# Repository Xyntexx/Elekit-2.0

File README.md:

# Elekit-2.0

[Auto generated schematic](output/schematic.pdf)

https://dl.espressif.com/dl/schematics/SCH_ESP32-C3-DEVKITC-02_V1_1_20210126A.pdf

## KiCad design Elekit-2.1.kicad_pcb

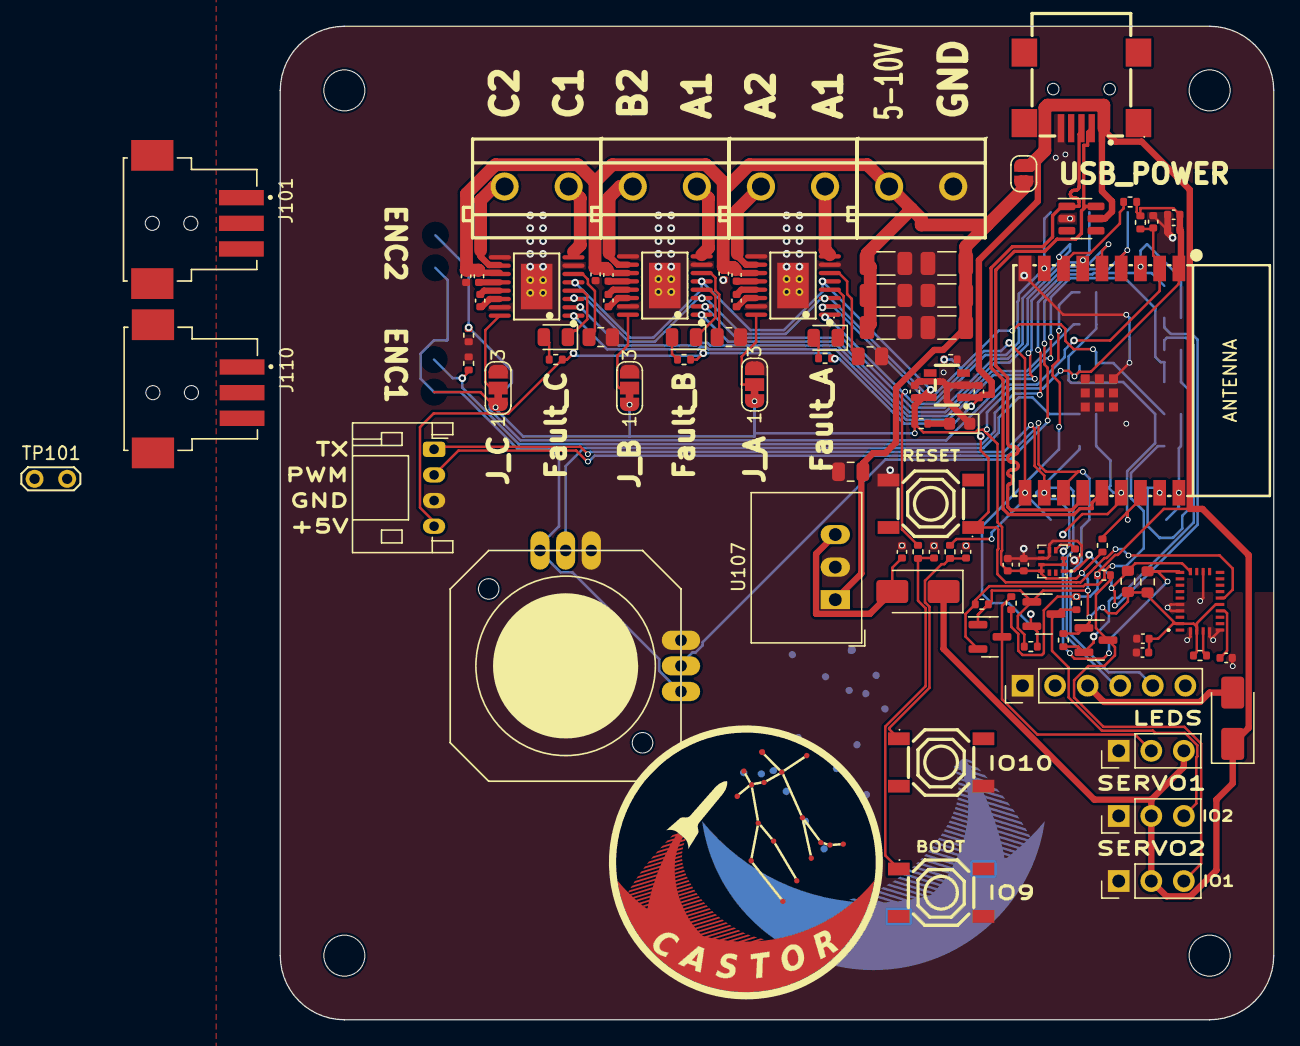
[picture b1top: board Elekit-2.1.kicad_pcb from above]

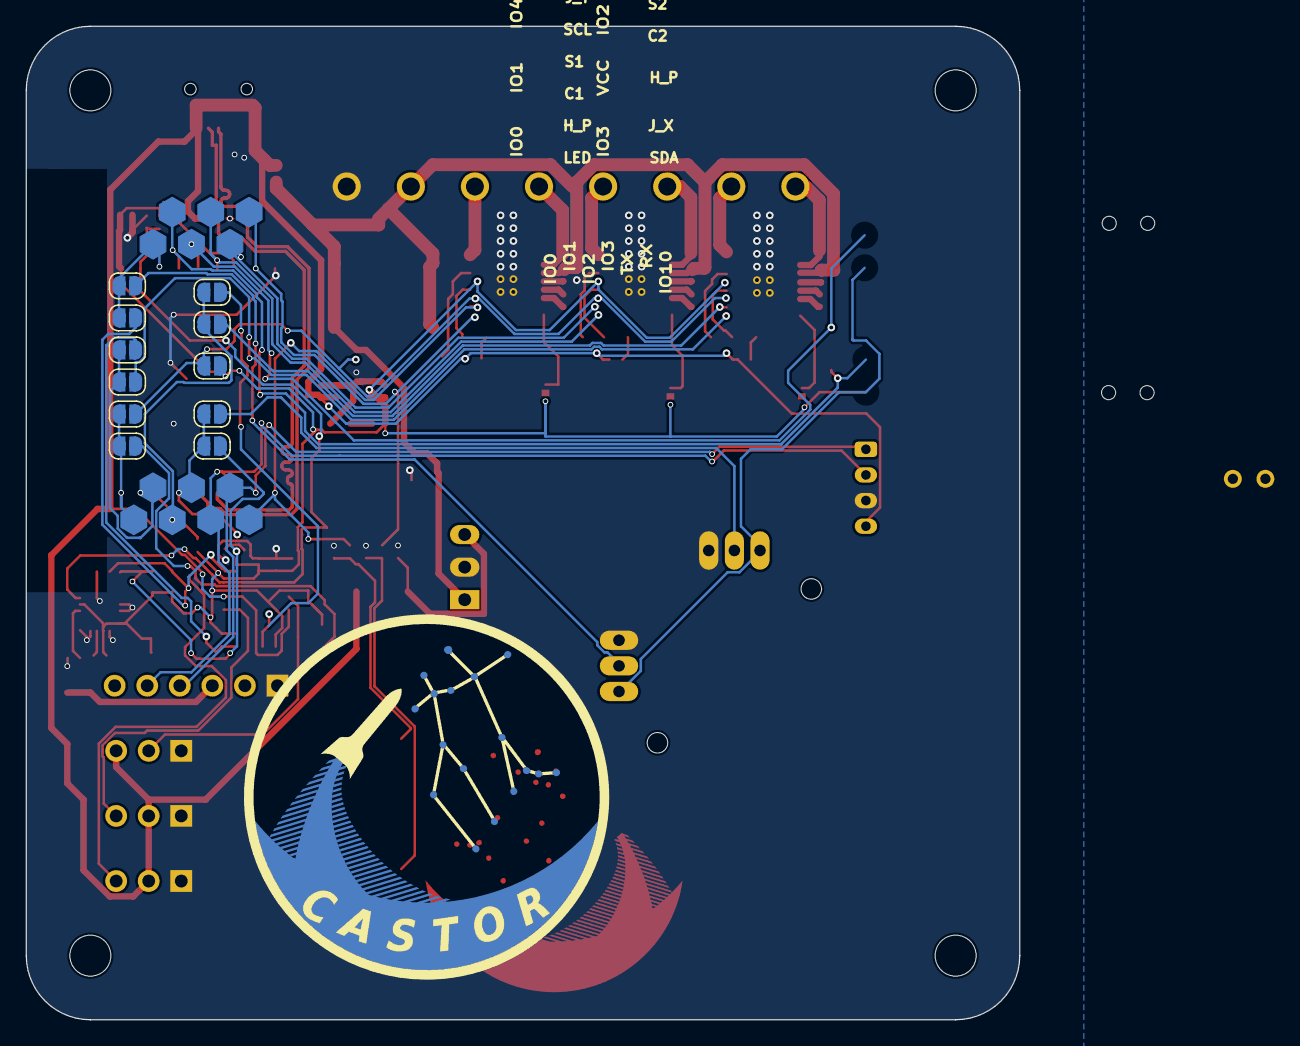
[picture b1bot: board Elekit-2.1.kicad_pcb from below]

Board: 2 copper layers, 77.5 x 77.5 mm, 123 parts (25 on the bottom side), 68 nets.

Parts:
C8, C9: 1u 25V; C_0402_1005Metric
C101, C102, C118: 22n 50V; C_0402_1005Metric
C103, C104, C105, C106, C112, C114, C116, C117, C119, C120, C125, C126, C127, C128: 100n 16V; C_0402_1005Metric
C107, C108, C109, C110, C121, C122: 47u 10V; C_1206_3216Metric
C111, C115: 10u 6.3V; C_0402_1005Metric
C113: 220n 16V; C_0402_1005Metric
C123: 0.47u 50v; C_0805_2012Metric
C124: 0.1u 50V; C_0402_1005Metric
D4: LED Emerald; LED_0603_1608Metric
D8, D104: SS34; D_SMA
D101, D102, D103: LED; LED_0805_2012Metric
H1, H2, H3, H4: MountingHole_Pad; MountingHole_3.2mm_M3
IC101: BNO085
J2, J3, J4, J103: Screw_Terminal_01x02; CONN-TH_P5.00_KF301-5.0-2P
J5, J9, J104: Conn_01x03_Male; PinHeader_1x03_P2.54mm_Vertical
J6: Conn_01x06_Male; PinHeader_1x06_P2.54mm_Vertical
J101, J110: Conn_01x03_Socket; TE_292173-3
J105, J106, J107, J108, J111, J112, J113, J117, J118, J119, J120, J121, J122: Conn_01x01_Pin; Hex Pad
J109: Conn_01x04_Socket; JST_PH_S4B-PH-K_1x04_P2.00mm_Horizontal
JP101, JP102, JP103, JP104, JP108, JP109, JP110, JP111, JP112, JP113, JP114, JP115: VIN DIODE BYPASS; SolderJumper-2_P1.3mm_Open_RoundedPad1.0x1.5mm
JP105, JP106, JP107: SolderJumper_3_Bridged12; SolderJumper-3_P1.3mm_Bridged12_RoundedPad1.0x1.5mm_NumberL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
LOGO1: CASTOR; Castor logo (2)
LOGO101: CASTOR; Castor logo (3)
Q1, Q3, Q101: 2N7002; SOT-23
R101, R102, R115, R118, R120, R121: 1k; R_0402_1005Metric
R103, R106, R107, R108, R109, R110, R111, R112, R113, R114, R116, R117, R124: 10k; R_0402_1005Metric
R104, R105, R119: 1k5; R_0805_2012Metric
R122, R123: 3k9; R_0603_1608Metric
RV101: R_Potentiometer_Dual; JOYSTICK_ANALOG_MINITHM
TP101: TestPoint_2Pole; TestPoint_2Pads_Pitch2.54mm_Drill0.8mm
U1: MINI_5PTP; MINI-USB-SMD_MINI-5PTP
U5: SRV05-4-P-T7; SOT-23-6
U7: ME6211C33M5G-N; SOT-23-5_L3.0-W1.7-P0.95-LS2.8-BR
U8, U10, U106: TS-1187A-B-A-B; SW-SMD_4P-L5.1-W5.1-P3.70-LS6.5-TL-2
U9: ESP32-C3-WROOM-02-N4(4MB); BULETM-SMD_ESPRESSIF_ESP32-C3-WROOM-02-N4-4MB
U101, U102, U104: DRV8876PWPR; HTSSOP-16_L5.0-W4.4-P0.65-LS6.4-BL-EP
U103: LSM303AGRTR; LGA-12_L2.0-W2.0-P0.50-BL
U107: R-78E5.0-0.5; Converter_DCDC_RECOM_R-78E-0.5_THT

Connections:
+3.3V: C9.1, C111.1, C112.1, C114.1, C115.2, C126.2, C127.2, IC101.3 (VDD), IC101.10 (CLKSEL0), IC101.28 (VDDIO), J101.1, J110.1, JP105.1 (A), JP106.1 (A), JP107.1 (A), JP115.2 (B), Q1.1 (G), Q3.1 (G), Q101.1 (G), R106.1, R107.2, R108.1, R109.1, R112.1, R113.1, R115.1, R122.1, R123.1, R124.1, RV101.1, RV101.6, U7.5 (VOUT), U9.1 (3V3), U101.5 (VREF), U102.5 (VREF), U103.2 (CS_XL), U103.3 (CS_MAG), U103.9 (Vdd), U103.10 (Vdd_IO), U104.5 (VREF)
+5V: C8.2, D8.1 (K), D104.1 (K), J5.2, J9.2, J104.3, J109.4, JP108.2 (B), R101.2, R102.2, R110.1, R111.1, R114.1, R118.2, U1.1 (VCC), U5.5 (VP), U7.1 (VIN)
+BATT: C103.2, C104.1, C105.2, C106.1, C107.2, C108.2, C109.2, C110.2, C119.2, C120.1, C121.2, C122.2, C123.2, J4.2, JP108.1 (A), U101.11 (VM), U102.11 (VM), U104.11 (VM), U107.1 (IN)
/A1: J2.1, U101.8 (OUT1)
/A1_C: J122.1, R120.1, U9.8 (IO9), U101.1 (EN/IN1)
/A2: J2.2, U101.10 (OUT2)
/A2_C: J105.1, R121.1, U9.10 (IO10), U101.2 (PH/IN2)
/A_analog: R105.2, U101.6 (IPROPI)
/B1: J3.1, U102.8 (OUT1)
/B1_C: J120.1, U9.6 (IO7), U102.1 (EN/IN1)
/B2: J3.2, U102.10 (OUT2)
/B2_C: J121.1, R107.1, U9.7 (IO8), U102.2 (PH/IN2)
/B_analog: R104.1, U102.6 (IPROPI)
/C1: J103.1, U104.8 (OUT1)
/C1_C: JP102.1 (A), U104.1 (EN/IN1)
/C2: J103.2, U104.10 (OUT2)
/C2_C: JP104.1 (A), U104.2 (PH/IN2)
/CHIP_PU: C117.2, IC101.11 (NRST), R106.2, U9.2 (EN), U10.1 (A)
/C_analog: R119.1, U104.6 (IPROPI)
/D+: U1.3 (D+), U5.1 (IO1), U9.14 (IO19)
/D-: U1.2 (D-), U5.6 (IO4), U9.13 (IO18)
/GPIO0: J113.1, JP113.2 (B), JP114.2 (B), U9.18 (IO0)
/GPIO1: J111.1, JP101.2 (B), JP102.2 (B), U9.17 (IO1)
/GPIO2: J112.1, JP103.2 (B), JP104.2 (B), R108.2, U9.16 (IO2)
/GPIO3: J108.1, JP109.2 (B), JP110.2 (B), U9.15 (IO3)
/GPIO4: J117.1, JP111.2 (B), JP112.2 (B), U9.3 (IO4)
/GPIO5: J101.2, J118.1, R117.2, U9.4 (IO5)
/GPIO6: J110.2, J119.1, R116.1, U9.5 (IO6)
/H-Bridge_nsleep: JP113.1 (A), JP115.1 (A), R103.1, U101.3 (nSLEEP), U102.3 (nSLEEP), U104.3 (nSLEEP)
/JoyX: JP109.1 (A), RV101.2
/JoyY: JP111.1 (A), RV101.5
/LED_in: JP114.1 (A), Q101.2 (S), R109.2
/LED_out: J104.2, Q101.3 (D), R110.2
/RX: J6.4, J106.1, J109.1, U9.11 (RXD)
/SCL: IC101.19 (H_SCL/SCK/RX), JP112.1 (A), R122.2, U103.1 (SCL/SPC)
/SDA: IC101.20 (H_SDA/H_MISO/TX_), JP110.1 (A), R123.2, U103.4 (SDA/SDI/SDO)
/SERVO1: J5.3, Q1.3 (D), R114.2
/SERVO1_C: JP101.1 (A), Q1.2 (S), R113.2
/SERVO2: J9.3, Q3.3 (D), R111.2
/SERVO2_C: JP103.1 (A), Q3.2 (S), R112.2
/TX: J6.5, J107.1, J109.2, U9.12 (TXD)
GND: C8.1, C9.2, C103.1, C105.1, C107.1, C108.1, C109.1, C110.1, C111.2, C112.2, C113.1, C114.2, C115.1, C116.1, C117.1, C119.1, C121.1, C122.1, C123.1, C124.1, C125.1, C126.1, C127.1, C128.1, D4.1 (K), IC101.2 (GND_1), IC101.5 (PS1), IC101.6 (PS0/WAKE), IC101.17 (SA0/H_MOSI_), IC101.25 (GND_2), IC101.26 (XOUT32/CLKSEL1), J4.1, J5.1, J6.1, J9.1, J101.3, J104.1, J109.3, J110.3, JP105.3 (B), JP106.3 (B), JP107.3 (B), R103.2, R104.2, R105.1, R116.2, R117.1, R119.2, RV101.3, RV101.4, TP101.1, U1.5 (GND), U5.2 (VN), U7.2 (VSS), U8.4 (D), U9.9 (GND), U9.19 (EP), U10.4 (D), U101.7 (IMODE), U101.9 (PGND), U101.15 (GND), U101.17 (EP), U102.7 (IMODE), U102.9 (PGND), U102.15 (GND), U102.17 (EP), U103.6 (GND), U103.8 (GND), U104.7 (IMODE), U104.9 (PGND), U104.15 (GND), U104.17 (EP), U106.4 (D), U107.2 (GND)
unnamed: D4.2 (A), R115.2
unnamed: D8.2 (A), J6.3
unnamed: D101.2 (A), R101.1
unnamed: D101.1 (K), U101.4 (nFAULT)
unnamed: D102.2 (A), R102.1
unnamed: D102.1 (K), U102.4 (nFAULT)
unnamed: D103.2 (A), R118.1
unnamed: D103.1 (K), U104.4 (nFAULT)
unnamed: C124.2, D104.2 (A), U107.3 (OUT)
unnamed: IC101.4 (BOOTN), R124.2, TP101.2
unnamed: C128.2, IC101.9 (CAP)
unnamed: JP105.2 (C), U102.16 (PMODE)
unnamed: JP106.2 (C), U101.16 (PMODE)
unnamed: JP107.2 (C), U104.16 (PMODE)
unnamed: C116.2, R120.2, U8.1 (A)
unnamed: C101.1, U101.13 (CPH)
unnamed: C101.2, U101.14 (CPL)
unnamed: C104.2, U101.12 (VCP)
unnamed: C102.1, U102.13 (CPH)
unnamed: C102.2, U102.14 (CPL)
unnamed: C106.2, U102.12 (VCP)
unnamed: C113.2, U103.5 (C1)
unnamed: C118.1, U104.13 (CPH)
unnamed: C118.2, U104.14 (CPL)
unnamed: C120.2, U104.12 (VCP)
unnamed: C125.2, R121.2, U106.1 (A)

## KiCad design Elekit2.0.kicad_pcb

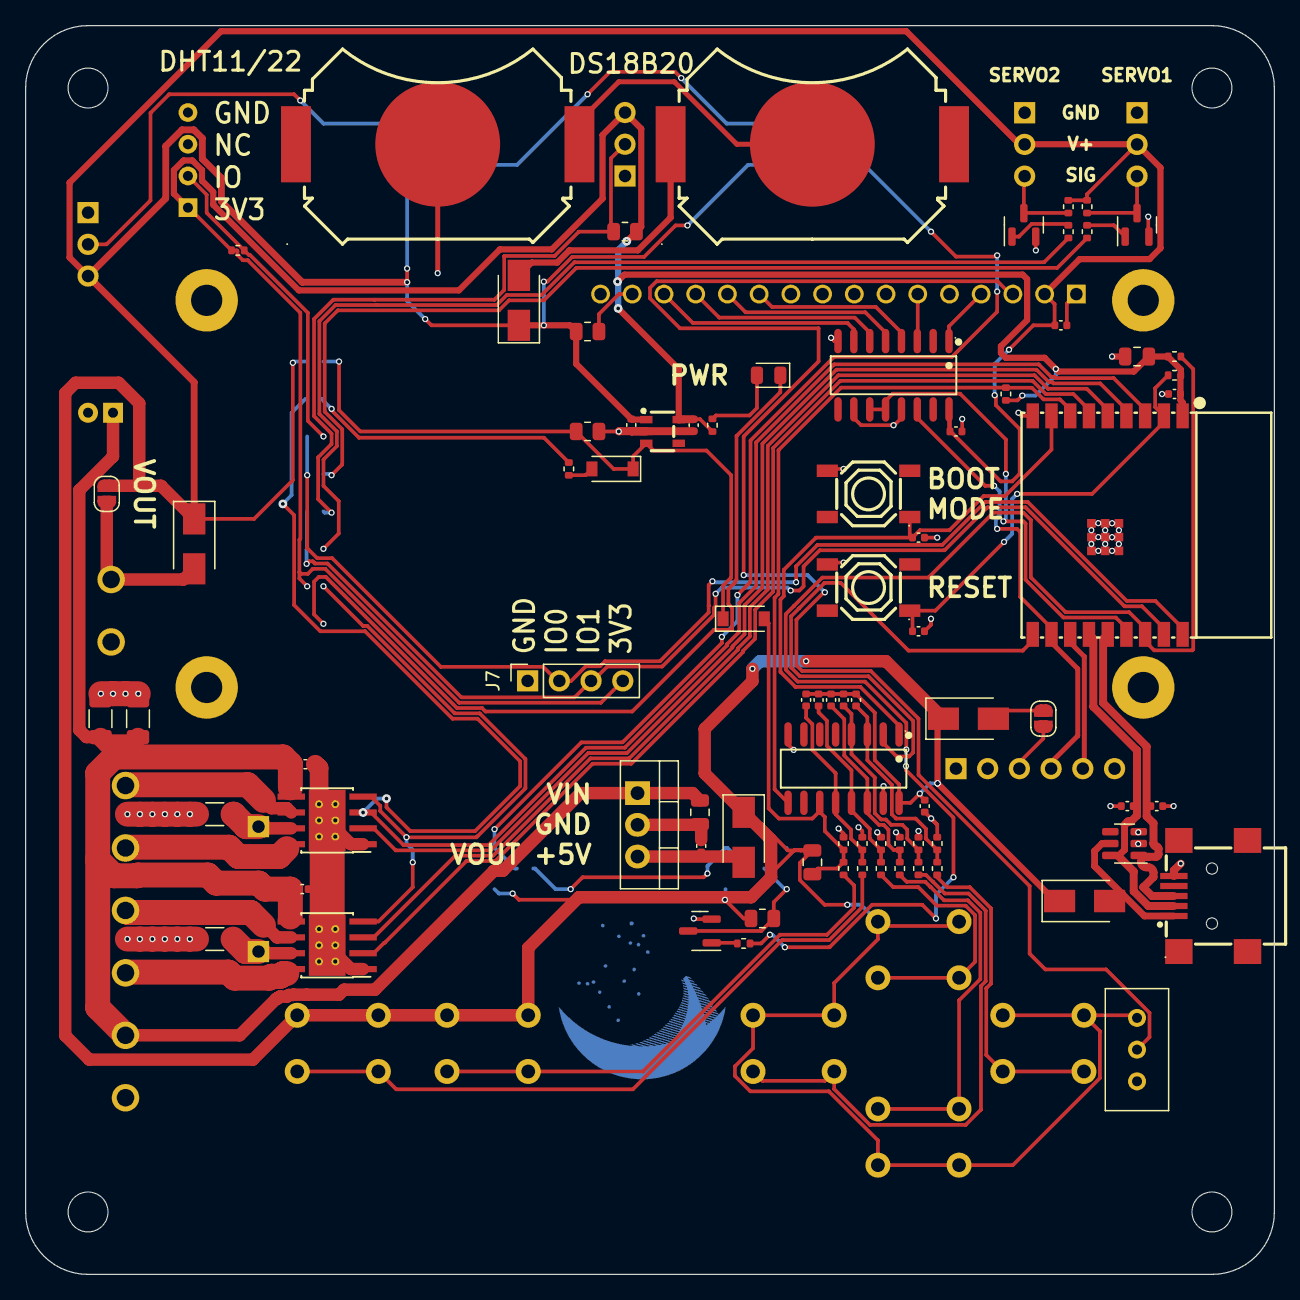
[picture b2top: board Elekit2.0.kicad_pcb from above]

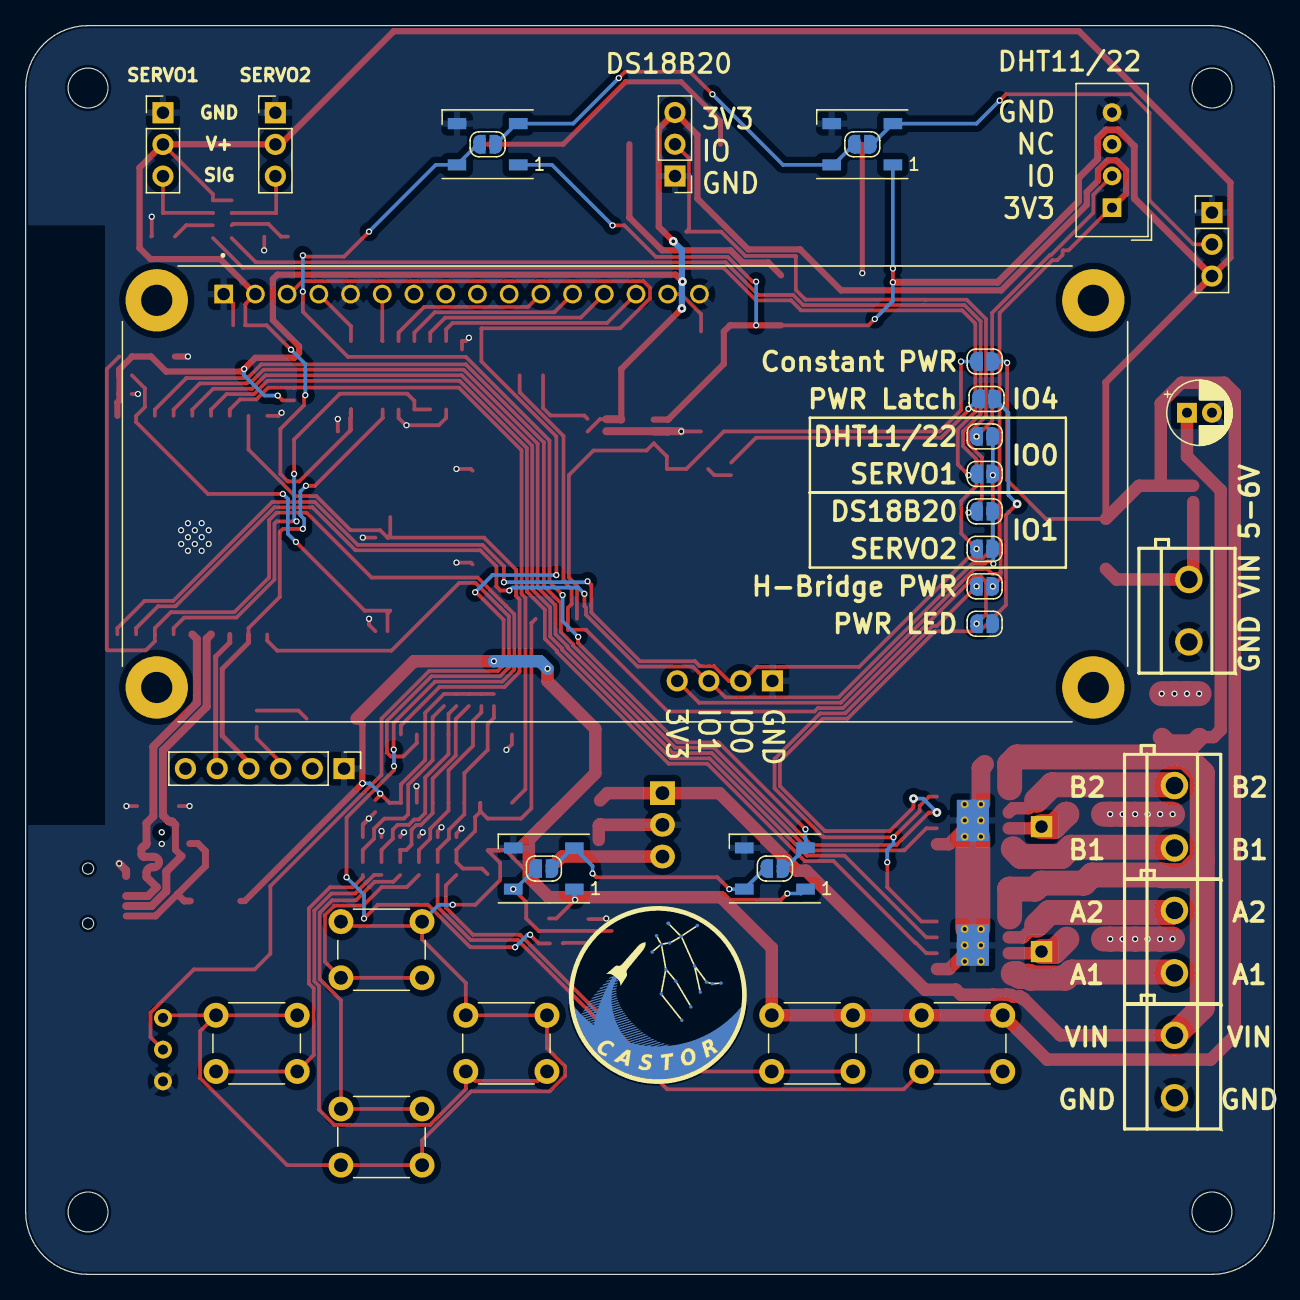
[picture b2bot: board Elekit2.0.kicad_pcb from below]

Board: 2 copper layers, 100.0 x 100.0 mm, 121 parts (35 on the bottom side), 73 nets.

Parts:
C1, C2, C5, C6, C7, C12, C13, C14, C15, C16, C17, C18, C20, C21, C22, C24: 0.1u 50V; C_0402_1005Metric
C4: 0.47u 50v; C_0805_2012Metric
C8, C9: 1u 25V; C_0402_1005Metric
C11: 10u; C_0805_2012Metric
C19, C23: 10u 50V; C_1206_3216Metric
C25: 1u; C_0805_2012Metric
C26: C_Polarized; CP_Radial_D5.0mm_P2.00mm
D1, D2, D3, D5, D8: SS34; D_SMA
D4: LED; LED_0805_2012Metric
D6, D7: 1N4148W; D_SOD-123
D9, D10, D11, D12: WS2812B; LED_WS2812B_PLCC4_5.0x5.0mm_P3.2mm
DS1: WC1602A; LCD_RC1602B-BIW-CSV
H1, H2, H3, H4: MountingHole_Pad; MountingHole_3.2mm_M3
J1, J2, J3, J4: Screw_Terminal_01x02; CONN-TH_P5.00_KF301-5.0-2P
J5, J9, J10: Conn_01x03_Male; PinHeader_1x03_P2.54mm_Vertical
J6: Conn_01x06_Male; PinHeader_1x06_P2.54mm_Vertical
J7: Conn_01x04; PinSocket_1x04_P2.54mm_Vertical
J11: DS18B20 temperature sensor; PinHeader_1x03_P2.54mm_Vertical
J12, J13: Conn_01x01_Male; PinHeader_1x01_P2.54mm_Vertical
JP1: Latch bypass; SolderJumper-2_P1.3mm_Open_RoundedPad1.0x1.5mm
JP2: VIN DIODE BYPASS; SolderJumper-2_P1.3mm_Open_RoundedPad1.0x1.5mm
JP3: H-Bridge; SolderJumper-2_P1.3mm_Open_RoundedPad1.0x1.5mm
JP4: PWR LED; SolderJumper-2_P1.3mm_Open_RoundedPad1.0x1.5mm
JP5, JP6, JP7, JP8, JP9: led bypass; SolderJumper-2_P1.3mm_Open_RoundedPad1.0x1.5mm
JP10, JP11, JP12, JP13: Servo1; SolderJumper-2_P1.3mm_Open_RoundedPad1.0x1.5mm
JP14: Latch control; SolderJumper-2_P1.3mm_Open_RoundedPad1.0x1.5mm
LOGO1: CASTOR; Castor logo
Q1, Q2, Q3: 2N7002; SOT-23
R2: 220R; R_0805_2012Metric
R3, R4, R5, R8, R9, R10, R13, R14, R20, R23, R24, R25, R26: 1k; R_0402_1005Metric
R6, R12, R15, R17, R18, R22, R28, R29, R30, R33: 10k; R_0402_1005Metric
R7: 1M; R_0805_2012Metric
R11: 5.1k; R_0805_2012Metric
R16: 4.7k; R_0805_2012Metric
R19, R21: 0R; R_1206_3216Metric
RV1: 10k; Potentiometer_Bourns_3296W_Vertical
SW1, SW2, SW3, SW4, SW5, SW6: SW_Push; SW_PUSH_6mm
U1: MINI_5PTP; MINI-USB-SMD_MINI-5PTP
U2, U4: MY-2032-12; BAT-SMD_MY-2032-12
U3: L7805; TO-220-3_Vertical
U5: SRV05-4-P-T7; SOT-23-6
U6: 74HC595; SOIC-16_L9.9-W3.9-P1.27-LS6.0-BL
U7: ME6211C33M5G-N; SOT-23-5_L3.0-W1.7-P0.95-LS2.8-BR
U8, U10: TS-1187A-B-A-B; SW-SMD_4P-L5.1-W5.1-P3.70-LS6.5-TL-2
U9: ESP32-C3-WROOM-02-N4(4MB); BULETM-SMD_ESPRESSIF_ESP32-C3-WROOM-02-N4-4MB
U11: DHT11; Aosong_DHT11_5.5x12.0_P2.54mm
U12, U15: DRV8870DDA; Texas_HTSOP-8-1EP_3.9x4.9mm_P1.27mm_EP2.95x4.9mm_Mask2.4x3.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
U13: 74HC165; SOIC-16_L9.9-W3.9-P1.27-LS6.0-BL

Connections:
+3.3V: C9.1, C11.1, C12.2, J7.4, J11.3, JP3.1 (A), R3.2, R12.2, R15.2, R16.1, R17.2, R18.1, U7.5 (VOUT), U9.1 (3V3), U11.1 (VCC)
+BATT: D1.2 (A), U2.1
/A1: J2.2, U15.6 (OUT1)
/A1_c: U9.5 (IO6), U15.3 (IN1)
/A2: J2.1, U15.8 (OUT2)
/A2_C: U9.6 (IO7), U15.2 (IN2)
/B1: J3.2, U12.6 (OUT1)
/B1_c: JP14.2 (B), U9.3 (IO4), U12.3 (IN1)
/B2: J3.1, U12.8 (OUT2)
/B2_C: U9.4 (IO5), U12.2 (IN2)
/BTN1: C25.1, D6.2 (A), R4.2, R6.1, U13.11 (D0)
/BTN2: C16.1, R20.2, R22.1, U13.12 (D1)
/BTN3: C17.1, R23.2, R28.1, U13.13 (D2)
/BTN4: C20.1, R24.2, R29.1, U13.14 (D3)
/BTN5: C21.1, R25.2, R30.1, U13.3 (D4)
/BTN6: C24.1, R26.2, R33.1, U13.4 (D5)
/CHIP_PU: C15.1, R12.1, U9.2 (EN), U10.1 (A)
/CLK1: U9.10 (IO10), U13.2 (CP)
/CLK2: U6.11 (SRCLK), U6.12 (RCLK), U9.15 (IO3)
/D+: C1.1, U1.3 (D+), U5.1 (IO1), U9.14 (IO19)
/D-: C2.2, U1.2 (D-), U5.6 (IO4), U9.13 (IO18)
/DHT_DATA: JP12.2 (B), R18.2, U11.2 (IO)
/DQ: J11.2, JP10.2 (B), R16.2
/EN_LDO: D6.1 (K), D7.1 (K), JP1.1 (A), R7.2, U7.3 (CE)
/GPIO0: J7.2, JP12.1 (A), JP13.1 (A), U9.18 (IO0)
/GPIO1: J7.3, JP10.1 (A), JP11.1 (A), U9.17 (IO1)
/GPIO2: R10.2, R15.1, U9.16 (IO2)
/GPIO8: R17.1, U9.7 (IO8), U13.9 (Q7)
/GPIO9: C13.1, U8.1 (A), U9.8 (IO9), U13.1 (~PL)
/H-BRIDGE_PWR: JP3.2 (B), U12.4 (VREF), U15.4 (VREF)
/HVBUS: C4.2, C18.2, C19.1, C22.2, C23.1, C26.1, J1.2, U3.1 (IN), U12.5 (VM), U15.5 (VM)
/Latch control: JP14.1 (A), R5.2
/RX: J6.4, U6.14 (SER), U9.11 (RXD)
/SERVO1: J5.3, Q1.3 (D), R9.2
/SERVO1_c: JP13.2 (B), R8.2
/SERVO2: J9.3, Q3.3 (D), R14.2
/SERVO2_c: JP11.2 (B), R13.2
/TX: J6.5, U9.12 (TXD)
/VBUS: C6.1, C7.1, C8.2, C14.1, C16.2, C17.2, C20.2, C21.2, C24.2, C25.2, D1.1 (K), D2.1 (K), D3.1 (K), D5.1 (K), D8.1 (K), D9.1 (VDD), D10.1 (VDD), D11.1 (VDD), D12.1 (VDD), DS1.2 (VDD), J5.2, J9.2, J10.3, JP1.2 (B), JP2.1 (A), R2.1, R9.1, R11.1, R14.1, RV1.3, SW1.2, SW2.1, SW3.1, SW4.1, SW5.1, SW6.1, U6.16 (VCC), U7.1 (VIN), U13.16 (VCC)
/VUSB: D3.2 (A), U1.1 (VCC), U5.5 (VP)
GND: C1.2, C2.1, C4.1, C5.1, C6.2, C7.2, C8.1, C9.2, C11.2, C12.1, C13.2, C14.2, C15.2, C18.1, C19.2, C22.1, C23.2, C26.2, D9.3 (VSS), D10.3 (VSS), D11.3 (VSS), D12.3 (VSS), DS1.1 (VSS), DS1.5 (R/W), DS1.16 (LED(-)), J1.1, J4.1, J5.1, J6.1, J7.1, J9.1, J10.1, J11.1, JP4.1 (A), Q1.2 (S), Q2.2 (S), Q3.2 (S), R6.2, R7.1, R19.2, R21.2, R22.2, R28.2, R29.2, R30.2, R33.2, RV1.1, U1.5 (GND), U3.2 (GND), U4.2, U5.2 (VN), U6.8 (GND), U6.10 (~SRCLR), U6.13 (~OE), U7.2 (VSS), U8.4 (D), U9.9 (GND), U9.19 (EP), U10.4 (D), U11.4 (GND), U12.1 (GND), U12.9 (GND), U13.8 (GND), U13.15 (~CE), U15.1 (GND), U15.9 (GND)
unnamed: C5.2, D2.2 (A), U3.3 (OUT)
unnamed: D4.1 (K), JP4.2 (B)
unnamed: D4.2 (A), R3.1
unnamed: D5.2 (A), J4.2, JP2.2 (B)
unnamed: D7.2 (A), R5.1
unnamed: D8.2 (A), JP5.2 (B)
unnamed: D9.4 (DIN), JP6.1 (A), Q2.3 (D), R11.2
unnamed: D10.2 (DOUT), D11.4 (DIN), JP7.2 (B), JP8.1 (A)
unnamed: D9.2 (DOUT), D10.4 (DIN), JP6.2 (B), JP7.1 (A)
unnamed: D11.2 (DOUT), D12.4 (DIN), JP8.2 (B), JP9.1 (A)
unnamed: D12.2 (DOUT), J10.2, JP9.2 (B)
unnamed: DS1.3 (VO), RV1.2
unnamed: DS1.4 (RS), U6.1 (QB)
unnamed: DS1.6 (E), U6.3 (QD)
unnamed: DS1.11 (D4), U6.4 (QE)
unnamed: DS1.12 (D5), U6.5 (QF)
unnamed: DS1.13 (D6), U6.6 (QG)
unnamed: DS1.14 (D7), U6.7 (QH)
unnamed: DS1.15 (LED(+)), R2.2
unnamed: J6.3, JP5.1 (A)
unnamed: J12.1, R21.1, U12.7 (ISEN)
unnamed: J13.1, R19.1, U15.7 (ISEN)
unnamed: Q1.1 (G), R8.1
unnamed: Q2.1 (G), R10.1
unnamed: Q3.1 (G), R13.1
unnamed: R4.1, SW1.1
unnamed: R20.1, SW2.2
unnamed: R23.1, SW3.2
unnamed: R24.1, SW4.2
unnamed: R25.1, SW5.2
unnamed: R26.1, SW6.2
unnamed: U2.2, U4.1

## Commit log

2022-10-20 Add files
2022-10-20 Add reference evaluation kit schematics to README file
2022-10-20 Added ESD protection for USB-C connector
2022-10-26 Remove old libaries
2022-10-26 Add a workflow to import JLCPCB symbols and footprints. Add symbols and footprints for components in schematic
2022-10-27 Add libraries for used JLCPCB parts. Replace used parts with JLCPCB parts. Start adding LCD support using a shift register
2022-11-11 Update libraries. Finish LCD connector. save before changing LDO
2022-12-10 Add new libraries
2022-12-10 remove unused files
2022-12-10 Add H bridge motor controllers and create first draft of pcb
2022-12-10 add unused modules
2022-12-21 Create first complete version
2023-01-22 Commit working file
2023-09-07 remove backups and Gerbers from repo
2023-09-07 remove more backups and gerbers from repo
2023-09-07 remove one more backup
2023-09-07 production updates
2023-09-07 update gitignore
2023-09-07 Update main.yml
    fix
2023-09-07 modify files for action testing
2023-09-07 Update PDFs [AUTO]
2023-09-07 Update main.yml
    [FORCE]
2023-09-07 test run pdf action
2023-10-09 update libraries
2023-10-09 Move old version to archive
2023-10-09 Complete version 2.1
2023-10-09 add interactive ui for adding jlcpcb parts
2023-10-26 add jst ph connector for lidar
2024-06-17 update libaries
2024-06-17 add bno085
